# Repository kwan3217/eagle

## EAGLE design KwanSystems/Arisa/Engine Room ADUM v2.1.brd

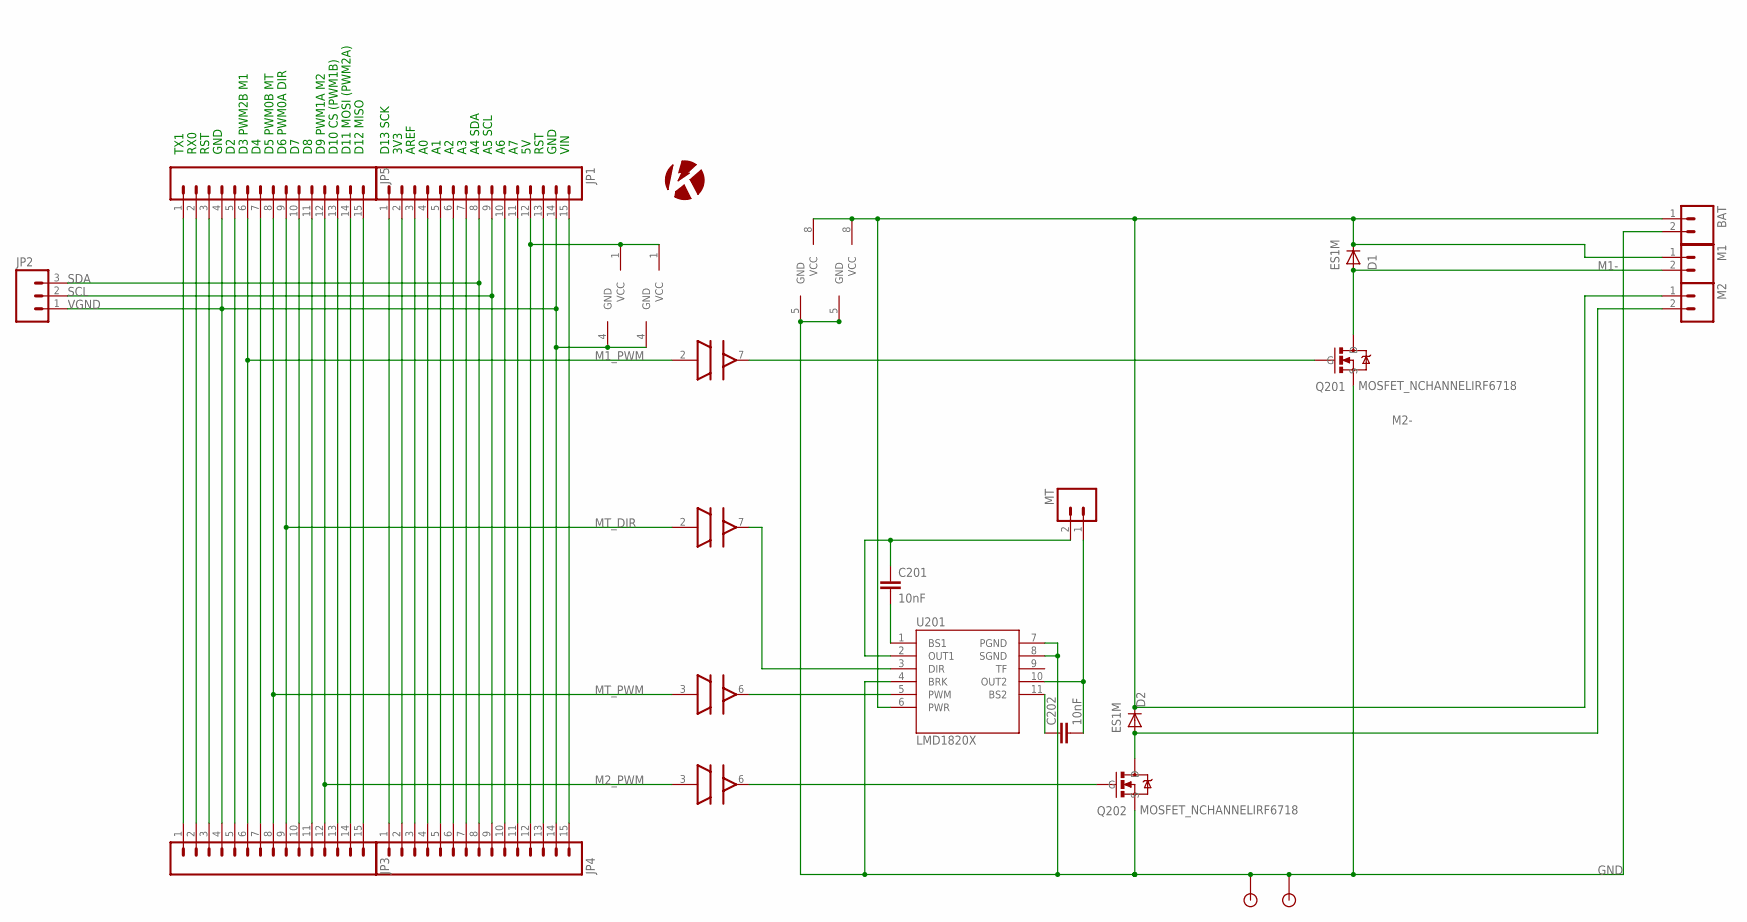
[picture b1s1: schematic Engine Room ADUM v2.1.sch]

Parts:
BAT: M02PTH4; 1X02_XTRA_BIG
C201, C202: 10nF; 0402-CAP
D1, D2: ES1M; DO-214AC
JP1, JP3, JP4, JP5: M15; 1X15
JP2: M03LOCK; 1X03_LOCK
M1, M2: M02PTH4; 1X02_XTRA_BIG
MT: M02PTH; 1X02
Q201, Q202: MOSFET_NCHANNELIRF6718; DIRECTFET_L6
U201: LMD1820X; TO-220-11LEAD
U$1: KWAN_CIRCLE
U$4, U$5: ADUM3221; SO8N
U$6, U$7: STANDOFF

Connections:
GND: BAT.2, Q201.S, Q202.S, U201.4 (BRK), U201.7 (PGND), U201.8 (SGND), U$4.5 (GND), U$5.5 (GND), U$6.P$1, U$7.P$1
M1-: D1.A, M1.2, Q201.D1 (D), Q201.D2 (D)
M1_PWM: JP3.6, JP5.6, U$4.2 (IN)
M2-: D2.A, M2.2, Q202.D1 (D), Q202.D2 (D)
M2_PWM: JP3.12, JP5.12, U$5.3 (IN)
MT_DIR: JP3.9, JP5.9, U$5.2 (IN)
MT_PWM: JP3.8, JP5.8, U$4.3 (IN)
unnamed: JP1.15, JP4.15
unnamed: Q201.G, U$4.7 (OUT)
unnamed: C202.1, U201.11 (BS2)
unnamed: Q202.G, U$5.6 (OUT)
unnamed: C201.2, U201.1 (BS1)
unnamed: U201.3 (DIR), U$5.7 (OUT)
unnamed: JP3.1, JP5.1
unnamed: JP3.2, JP5.2
unnamed: JP3.3, JP5.3
unnamed: U201.5 (PWM), U$4.6 (OUT)
unnamed: C201.1, MT.2, U201.2 (OUT1)
unnamed: C202.2, MT.1, U201.10 (OUT2)
unnamed: JP3.5, JP5.5
unnamed: JP3.15, JP5.15
unnamed: JP3.14, JP5.14
unnamed: JP3.13, JP5.13
unnamed: JP3.7, JP5.7
unnamed: JP3.10, JP5.10
unnamed: JP3.11, JP5.11
unnamed: JP1.13, JP4.13
unnamed: JP1.11, JP4.11
unnamed: JP1.10, JP4.10
unnamed: JP1.7, JP4.7
unnamed: JP1.6, JP4.6
unnamed: JP1.5, JP4.5
unnamed: JP1.4, JP4.4
unnamed: JP1.3, JP4.3
unnamed: JP1.2, JP4.2
unnamed: JP1.1, JP4.1
SCL: JP1.9, JP2.2, JP4.9
SDA: JP1.8, JP2.3, JP4.8
VCC: JP1.12, JP4.12, U$4.1 (VCC), U$5.1 (VCC)
VDD: BAT.1, D1.C, D2.C, M1.1, M2.1, U201.6 (PWR), U$4.8 (VCC), U$5.8 (VCC)
VGND: JP1.14, JP2.1, JP3.4, JP4.14, JP5.4, U$4.4 (GND), U$5.4 (GND)

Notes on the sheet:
VIN
GND
RST
A5 SCL
A4 SDA
AREF
3V3
D13 SCK
D12 MISO
D11 MOSI (PWM2A)
D10 CS (PWM1B)
D9 PWM1A M2
D6 PWM0A DIR
D5 PWM0B MT
D3 PWM2B M1
RX0
TX1

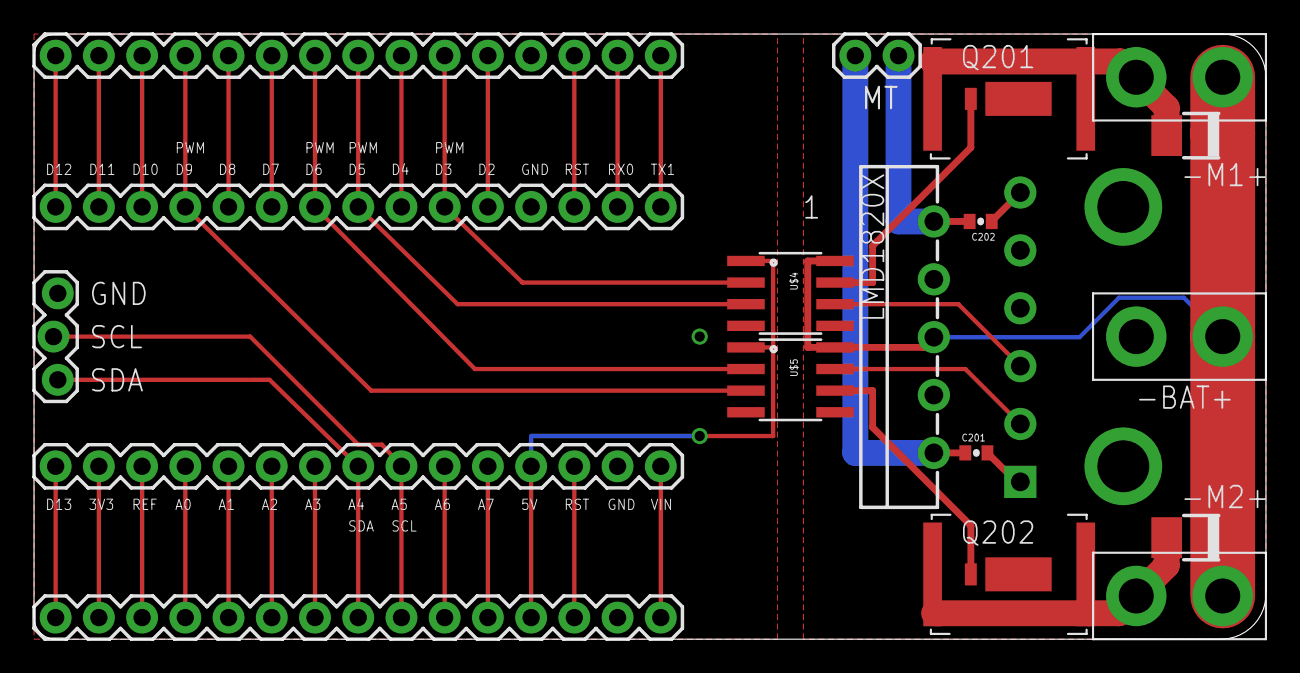
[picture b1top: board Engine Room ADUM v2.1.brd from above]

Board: 2 copper layers, 72.4 x 35.6 mm, 21 parts (1 on the bottom side), 41 nets.

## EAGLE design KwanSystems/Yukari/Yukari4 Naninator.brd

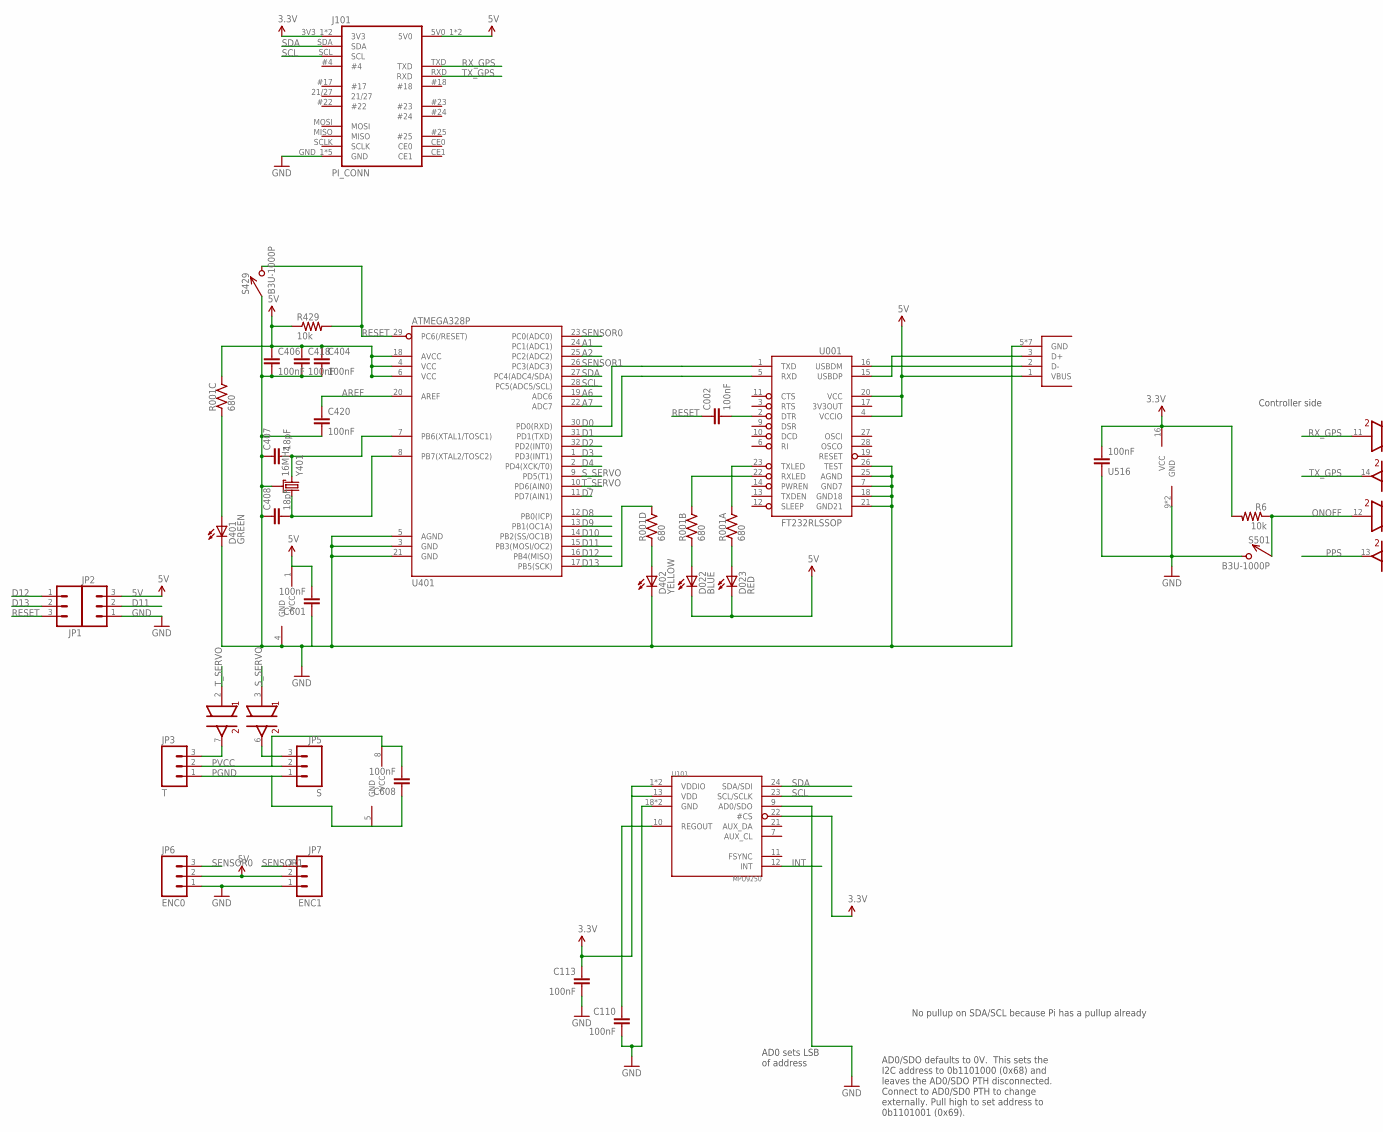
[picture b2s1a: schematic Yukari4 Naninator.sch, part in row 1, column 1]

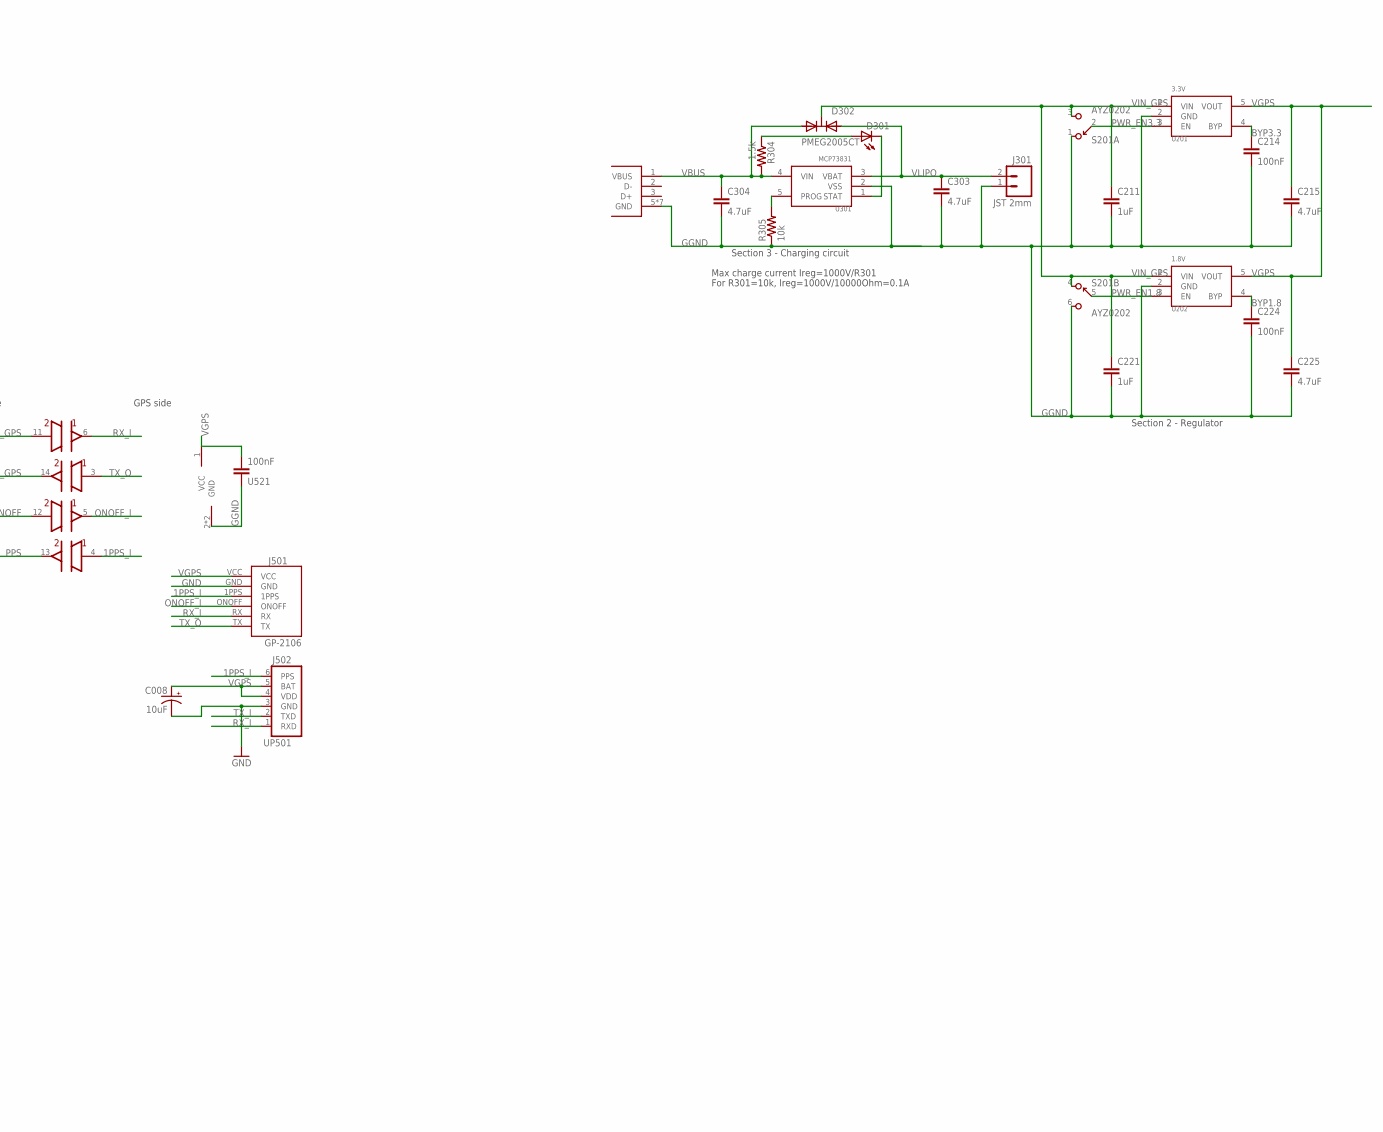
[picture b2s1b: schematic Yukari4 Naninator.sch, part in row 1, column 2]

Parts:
C002, C404, C406, C418, C420, C601, C608: 100nF; 0402-CAP; DIGIKEY 445-1268-1-ND
C008: 10uF; EIA3216
C110, C113: 100nF; 0402-CAP
C211, C221: 1uF; 0402-CAP; DIGIKEY 445-4114-1-ND
C214, C224: 100nF; 0402-CAP; DIGIKEY 445-1265-1-ND
C215, C225, C303, C304: 4.7uF; 0402-CAP; DIGIKEY 445-7395-1-ND
C407, C408: 18pF; 0402-CAP; DIGIKEY 445-1238-1-ND
D022: BLUE; LED-0603; DIGIKEY 350-2037-1-ND
D023: RED; LED-0603; DIGIKEY 754-1359-1-ND
D301: YELLOW; LED-0603; DIGIKEY 350-2032-1-ND
D302: PMEG2005CT; SOT-23-3
D401: GREEN; LED-0603; DIGIKEY 350-2036-1-ND
D402: YELLOW; LED-0603; DIGIKEY 754-1124-1-ND
J001, J302: USB_MICROB_JST; UB-MC5BR3-SD204-4S; DIGIKEY 455-2562-1-ND
J101: PI_CONN
J301: JST 2mm; JST-2-SMD; DIGIKEY 455-1749-1-ND
J501: GP-2106
J502: UP501
JP1, JP2: M03PTH; 1X03; DIGIKEY $NOPART
JP3: T; 1X03; DIGIKEY $NOPART
JP5: S; 1X03; DIGIKEY $NOPART
JP6: ENC0; 1X03; DIGIKEY $NOPART
JP7: ENC1; 1X03; DIGIKEY $NOPART
R001: 680; CRA04; DIGIKEY CRA4S8680CT-ND
R6: 10k; 0402-RES
R304: 1.5k; 0402-RES; DIGIKEY P1.50KLCT-ND
R305, R429: 10k; 0402-RES; DIGIKEY P10.0KLCT-ND
S201: AYZ0202
S429, S501: B3U-1000P
U001: FT232RLSSOP; SSOP28DB; DIGIKEY 768-1007-1-ND
U101: MPU9250; LQFN_3MM_3MM
U201: 3.3V; SOT-23-5; DIGIKEY 576-1910-1-ND
U202: 1.8V; SOT-23-5; DIGIKEY 576-1910-1-ND
U301: MCP73831; SOT-23-5; DIGIKEY 576-1910-1-ND
U401: ATMEGA328P; TQFP32-08; DIGIKEY ATMEGA328P-15AZCT-ND
U501: ADUM242E; 16-SOIC-W
U516, U521: 100nF; 0402-CAP; DIGIKEY 445-1268-1-ND
U601: ADUM3221; SO8N
Y401: 16MHz; CRYSTAL_SMD_2MM_2_5MM; DIGIKEY 478-6955-1-ND

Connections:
1PPS_I: J501.1PPS, J502.6 (PPS), U501.4 (IN)
3.3V: C113.1, J101.3V3_1 (3V3), J101.3V3_2 (3V3), R6.2, U101.1 (VDDIO), U101.8 (VDDIO), U101.13 (VDD), U101.22 (#CS), U501.16 (VCC), U516.2
5V: C404.1, C406.1, C418.1, C601.2, D022.C, D023.C, J001.1 (VBUS), J101.5V0_1 (5V0), J101.5V0_2 (5V0), JP2.3, JP6.2, JP7.2, R001.6 (2), R429.1, U001.4 (VCCIO), U001.20 (VCC), U401.4 (VCC), U401.6 (VCC), U401.18 (AVCC), U601.1 (VCC)
A1: U401.24 (PC1(ADC1))
A2: U401.25 (PC2(ADC2))
A6: U401.19 (ADC6)
A7: U401.22 (ADC7)
AREF: C420.1, U401.20 (AREF)
BYP1.8: C224.1, U202.4 (BYP)
BYP3.3: C214.1, U201.4 (BYP)
D0: U001.1 (TXD), U401.30 (PD0(RXD))
D1: U001.5 (RXD), U401.31 (PD1(TXD))
D2: U401.32 (PD2(INT0))
D3: U401.1 (PD3(INT1))
D4: U401.2 (PD4(XCK/T0))
D7: U401.11 (PD7(AIN1))
D8: U401.12 (PB0(ICP))
D9: U401.13 (PB1(OC1A))
D10: U401.14 (PB2(SS/OC1B))
D11: JP2.2, U401.15 (PB3(MOSI/OC2))
D12: JP1.1, U401.16 (PB4(MISO))
D13: JP1.2, R001.5 (2), U401.17 (PB5(SCK))
DTR#: C002.2, U001.2 (DTR)
GGND: C211.2, C214.2, C215.2, C221.2, C224.2, C225.2, C303.2, C304.2, J301.1, J302.5 (GND), J302.P$6 (GND), J302.P$7 (GND), J302.P$8 (GND), J302.P$9 (GND), J302.P$10 (GND), J302.P$11 (GND), R305.1, S201.1, S201.6, U201.2 (GND), U202.2 (GND), U301.2 (VSS), U501.2 (GND), U501.8 (GND), U521.1
GND: C008.C (-), C110.2, C113.2, C404.2, C406.2, C407.1, C408.1, C418.2, C420.2, C601.1, D401.C, D402.C, J001.5 (GND), J001.P$6 (GND), J001.P$7 (GND), J001.P$8 (GND), J001.P$9 (GND), J001.P$10 (GND), J001.P$11 (GND), J101.GND_1 (GND), J101.GND_2 (GND), J101.GND_3 (GND), J101.GND_4 (GND), J101.GND_5 (GND), J501.GND, J502.3 (GND), JP2.1, JP6.1, JP7.1, S429.P$1 (1), S501.P$2 (2), U001.7 (GND7), U001.18 (GND18), U001.21 (GND21), U001.25 (AGND), U001.26 (TEST), U101.9 (AD0/SDO), U101.18 (GND), U101.20 (GND), U401.3 (GND), U401.5 (AGND), U401.21 (GND), U501.9 (GND), U501.15 (GND), U516.1, U601.4 (GND), Y401.2 (GND), Y401.4 (GND)
INT: U101.12 (INT)
unnamed: C407.2, U401.7 (PB6(XTAL1/TOSC1)), Y401.3 (2)
unnamed: C408.2, U401.8 (PB7(XTAL2/TOSC2)), Y401.1
unnamed: J001.3 (D+), U001.15 (USBDP)
unnamed: J001.2 (D-), U001.16 (USBDM)
unnamed: D401.A, R001.3 (1)
unnamed: JP5.3, U601.6 (OUT)
unnamed: JP3.3, U601.7 (OUT)
unnamed: D402.A, R001.4 (1)
unnamed: D023.A, R001.1
unnamed: R305.2, U301.5 (PROG)
unnamed: D022.A, R001.2 (1)
unnamed: D301.C, U301.1 (STAT)
unnamed: D301.A, R304.1
ONOFF: R6.1, S501.P$1 (1), U501.12 (IN)
ONOFF_I: J501.ONOFF, U501.5 (OUT)
PGND: C608.1, JP3.1, JP5.1, U601.5 (GND)
PPS: U501.13 (OUT)
PVCC: C608.2, JP3.2, JP5.2, U601.8 (VCC)
PWR_EN1.8: S201.5, U202.3 (EN)
PWR_EN3.3: S201.2, U201.3 (EN)
REGOUT: C110.1, U101.10 (REGOUT)
RESET: C002.1, JP1.3, R429.2, S429.P$2 (2), U401.29 (PC6(/RESET))
RXLED1: R001.7 (2), U001.22 (RXLED)
RX_GPS: J101.TXD, U501.11 (IN)
RX_I: J501.RX, J502.1 (RXD), U501.6 (OUT)
SCL: J101.SCL, U101.23 (SCL/SCLK), U401.28 (PC5(ADC5/SCL))
SDA: J101.SDA, U101.24 (SDA/SDI), U401.27 (PC4(ADC4/SDA))
SENSOR0: JP6.3, U401.23 (PC0(ADC0))
SENSOR1: JP7.3, U401.26 (PC3(ADC3))
S_SERVO: U401.9 (PD5(T1)), U601.3 (IN)
TXLED1: R001.8 (2), U001.23 (TXLED)
TX_GPS: J101.RXD, U501.14 (OUT)
TX_I: J502.2 (TXD)
TX_O: J501.TX, U501.3 (IN)
T_SERVO: U401.10 (PD6(AIN0)), U601.2 (IN)
VBUS: C304.1, D302.1 (A1), J302.1 (VBUS), R304.2, U301.4 (VIN)
VGPS: C008.A (+), C215.1, C225.1, J501.VCC, J502.4 (VDD), J502.5 (BAT), U201.5 (VOUT), U202.5 (VOUT), U501.1 (VCC), U521.2
VIN_GPS: C211.1, C221.1, D302.3 (K), S201.3, S201.4, U201.1 (VIN), U202.1 (VIN)
VLIPO: C303.1, D302.2 (A2), J301.2, U301.3 (VBAT)

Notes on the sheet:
AD0/SDO defaults to 0V. This sets the I2C address to 0b1101000 (0x68) and leaves the AD0/SDO PTH disconnected. Connect to AD0/SD0 PTH to change externally. Pull high to set address to 0b1101001 (0x69).
AD0 sets LSB of address
No pullup on SDA/SCL because Pi has a pullup already
GPS side
Controller side
Section 3 - Charging circuit
Max charge current Ireg=1000V/R301
For R301=10k, Ireg=1000V/10000Ohm=0.1A
Section 2 - Regulator

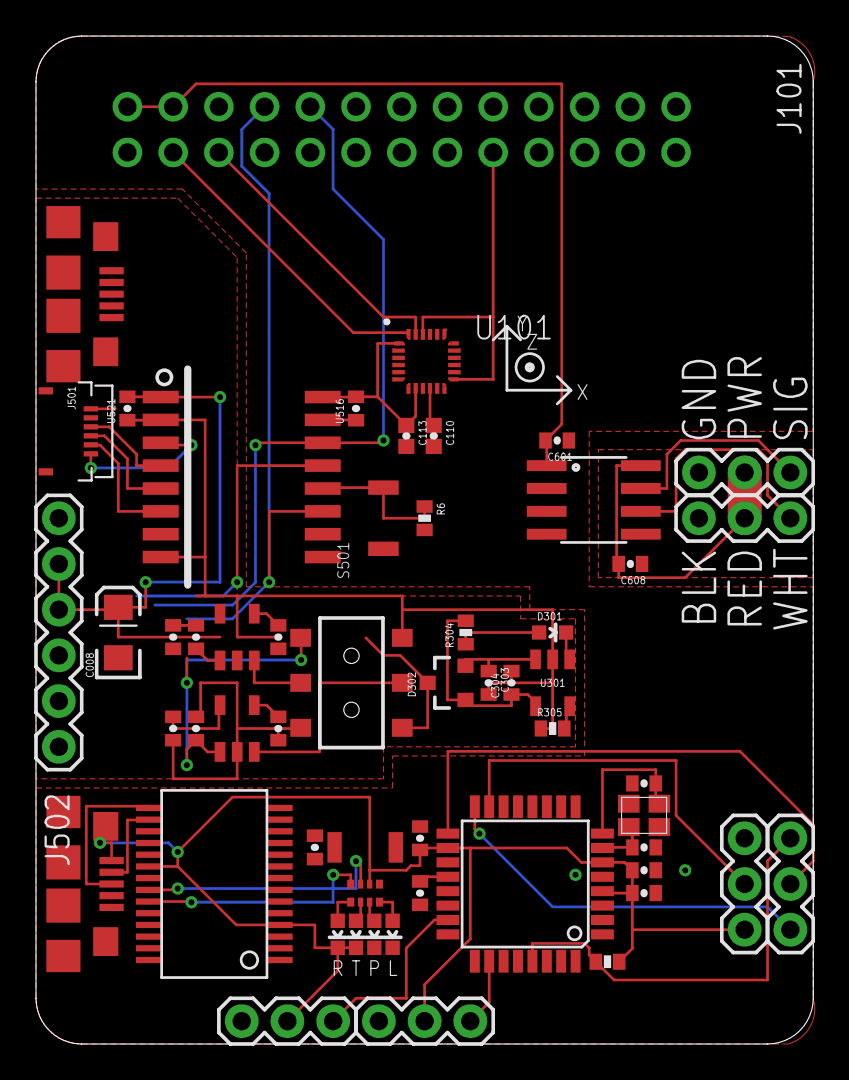
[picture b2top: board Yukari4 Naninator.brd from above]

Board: 2 copper layers, 43.2 x 56.0 mm, 58 parts (1 on the bottom side), 51 nets.

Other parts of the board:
U$2: AXES

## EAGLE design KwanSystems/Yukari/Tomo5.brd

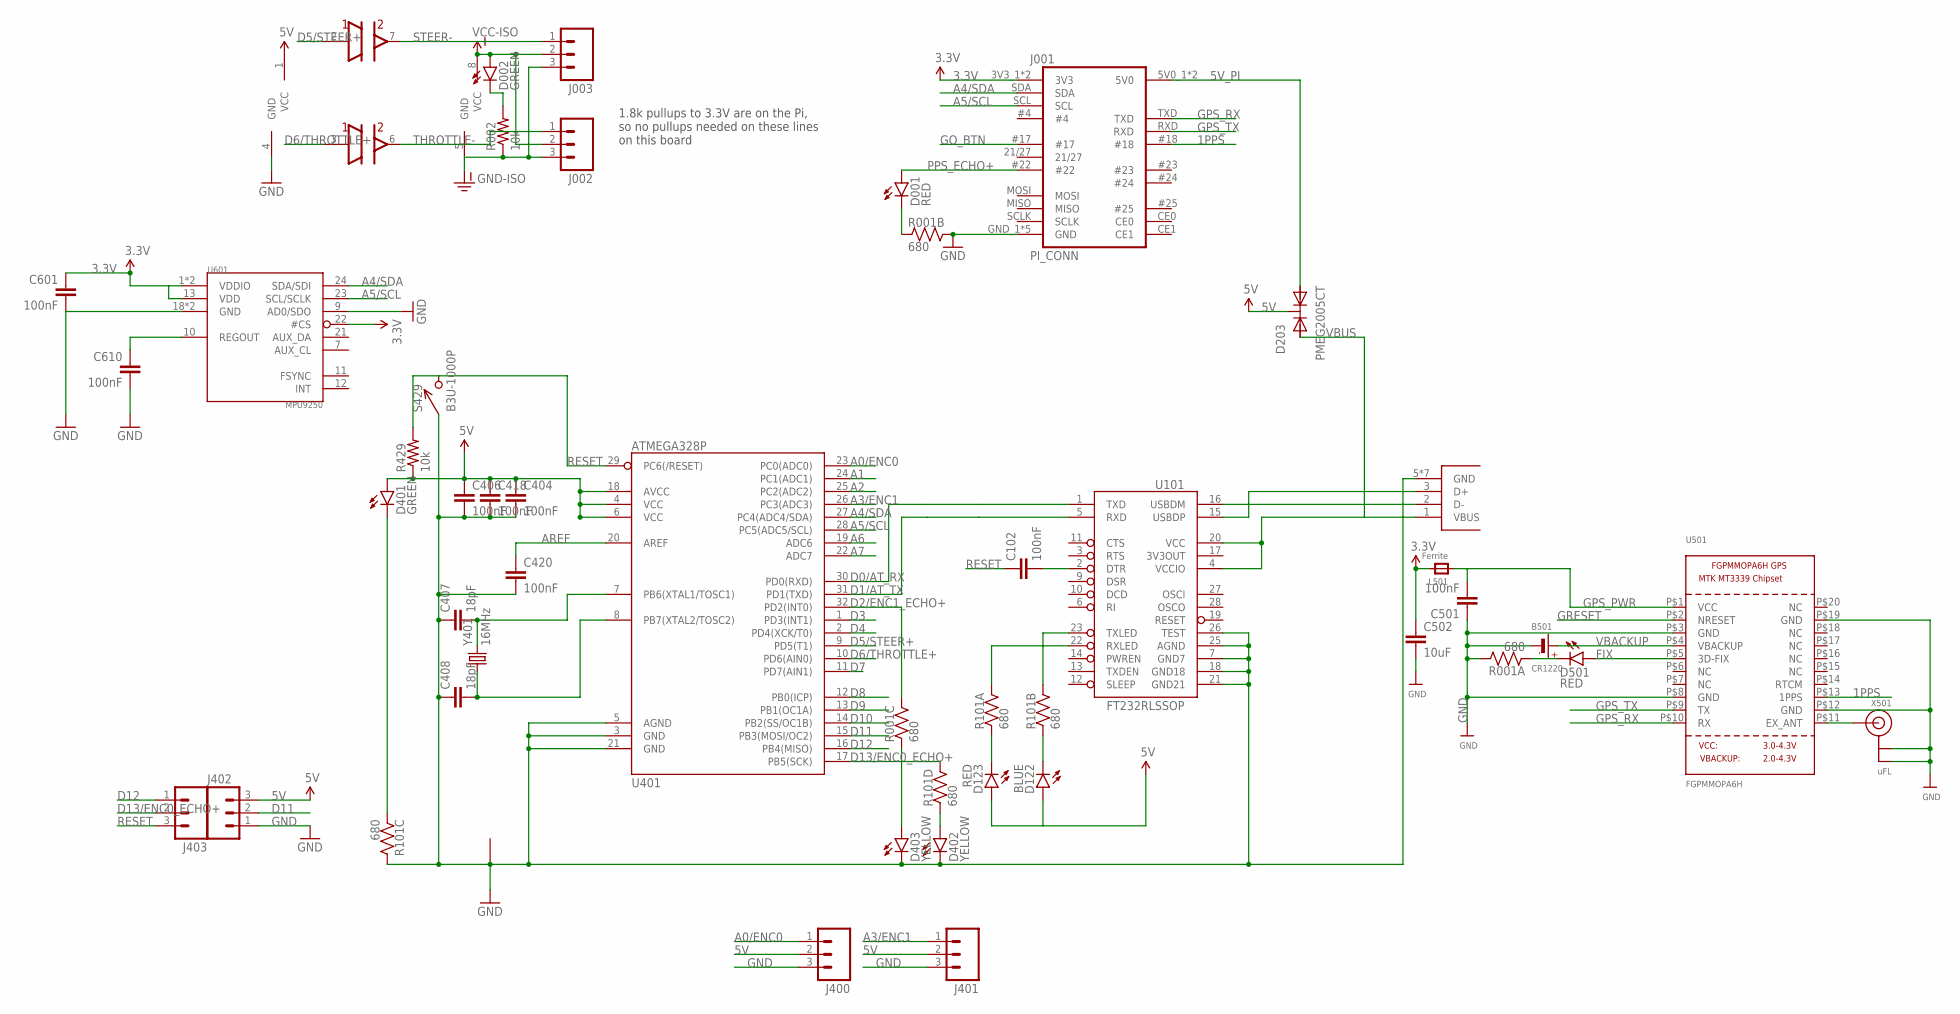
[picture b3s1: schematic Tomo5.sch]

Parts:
B501: CR1220; CR1220-2
C102, C404, C406, C418, C420, C501: 100nF; 0402-CAP; DIGIKEY 445-1268-1-ND
C407, C408: 18pF; 0402-CAP; DIGIKEY 445-1238-1-ND
C502: 10uF; 1206
C601: 100nF; 0603-CAP
C610: 100nF; 0402-CAP
D001, D501: RED; LED-0603
D002, D401: GREEN; LED-0603; DIGIKEY 350-2036-1-ND
D122: BLUE; LED-0603; DIGIKEY 350-2037-1-ND
D123: RED; LED-0603; DIGIKEY 754-1359-1-ND
D203: PMEG2005CT; SOT-23-3
D402, D403: YELLOW; LED-0603; DIGIKEY 754-1124-1-ND
J001: PI_CONN
J002, J003, J400, J401, J402, J403: M03PTH; 1X03; DIGIKEY $NOPART
J101: USB_MICROB_JST; UB-MC5BR3-SD204-4S; DIGIKEY 455-2562-1-ND
L501: Ferrite; 0805-NO
R001, R101: 680; CRA04; DIGIKEY CRA4S8680CT-ND
R002, R429: 10k; 0402-RES; DIGIKEY P10.0KLCT-ND
S429: B3U-1000P
U101: FT232RLSSOP; SSOP28DB; DIGIKEY 768-1007-1-ND
U401: ATMEGA328P; TQFP32-08; DIGIKEY ATMEGA328P-15AZCT-ND
U501: FGPMMOPA6H
U601: MPU9250; LQFN_3MM_3MM
U$7: ADUM3221; SO8N
X501: uFL; U.FL
Y401: 16MHz; CRYSTAL_SMD_2MM_2_5MM; DIGIKEY 478-6955-1-ND

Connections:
1PPS: J001.#18, U501.P$13 (1PPS)
3.3V: C502.1, C601.1, J001.3V3_1 (3V3), J001.3V3_2 (3V3), L501.2, U601.1 (VDDIO), U601.8 (VDDIO), U601.13 (VDD), U601.22 (#CS)
5V: C404.1, C406.1, C418.1, D122.A, D123.A, D203.3 (K), D401.A, J400.2, J401.2, J402.3, R429.1, U401.4 (VCC), U401.6 (VCC), U401.18 (AVCC), U$7.1 (VCC)
5V_PI: D203.1 (A1), J001.5V0_1 (5V0), J001.5V0_2 (5V0)
A0/ENC0: J400.1, U401.23 (PC0(ADC0))
A1: U401.24 (PC1(ADC1))
A2: U401.25 (PC2(ADC2))
A3/ENC1: J401.1, U401.26 (PC3(ADC3))
A4/SDA: J001.SDA, U401.27 (PC4(ADC4/SDA)), U601.24 (SDA/SDI)
A5/SCL: J001.SCL, U401.28 (PC5(ADC5/SCL)), U601.23 (SCL/SCLK)
A6: U401.19 (ADC6)
A7: U401.22 (ADC7)
AREF: C420.1, U401.20 (AREF)
D0/AT_RX: U101.1 (TXD), U401.30 (PD0(RXD))
D1/AT_TX: U101.5 (RXD), U401.31 (PD1(TXD))
D2/ENC1_ECHO+: R001.6 (2), U401.32 (PD2(INT0))
D3: U401.1 (PD3(INT1))
D4: U401.2 (PD4(XCK/T0))
D5/STEER+: U401.9 (PD5(T1)), U$7.2 (IN)
D6/THROTTLE+: U401.10 (PD6(AIN0)), U$7.3 (IN)
D7: U401.11 (PD7(AIN1))
D8: U401.12 (PB0(ICP))
D9: U401.13 (PB1(OC1A))
D10: U401.14 (PB2(SS/OC1B))
D11: J402.2, U401.15 (PB3(MOSI/OC2))
D12: J403.1, U401.16 (PB4(MISO))
D13/ENC0_ECHO+: J403.2, R101.5 (2), U401.17 (PB5(SCK))
DTR#: C102.2, U101.2 (DTR)
ENC0_ECHO-: D402.A, R101.4 (1)
FIX: D501.A, U501.P$5 (3D-FIX)
GND: B501.-, C404.2, C406.2, C407.1, C408.1, C418.2, C420.2, C501.1, C502.2, C601.2, C610.2, D402.C, D403.C, J001.GND_1 (GND), J001.GND_2 (GND), J001.GND_3 (GND), J001.GND_4 (GND), J001.GND_5 (GND), J101.5 (GND), J101.P$6 (GND), J101.P$7 (GND), J101.P$8 (GND), J101.P$9 (GND), J101.P$10 (GND), J101.P$11 (GND), J400.3, J401.3, J402.1, R001.7 (2), R001.8 (2), R101.6 (2), S429.P$1 (1), U101.7 (GND7), U101.18 (GND18), U101.21 (GND21), U101.25 (AGND), U101.26 (TEST), U401.3 (GND), U401.5 (AGND), U401.21 (GND), U501.P$3 (GND), U501.P$8 (GND), U501.P$12 (GND), U501.P$19 (GND), U601.9 (AD0/SDO), U601.18 (GND), U601.20 (GND), U$7.4 (GND), X501.1 (GND), X501.2 (GND), Y401.2 (1), Y401.4 (1)
GND-ISO: J002.3, J003.3, R002.1, U$7.5 (GND)
GO_BTN: J001.#17
GPS_PWR: C501.2, L501.1, U501.P$1 (VCC)
GPS_RX: J001.TXD, U501.P$10 (RX)
GPS_TX: J001.RXD, U501.P$9 (TX)
GRESET: U501.P$2 (NRESET)
IPWR-: D002.C, R002.2
unnamed: C407.2, U401.7 (PB6(XTAL1/TOSC1)), Y401.3 (2)
unnamed: C408.2, U401.8 (PB7(XTAL2/TOSC2)), Y401.1
unnamed: J101.3 (D+), U101.15 (USBDP)
unnamed: J101.2 (D-), U101.16 (USBDM)
unnamed: D401.C, R101.3 (1)
unnamed: D501.C, R001.1
unnamed: U501.P$11 (EX_ANT), X501.3 (SIGNAL)
unnamed: D403.A, R001.3 (1)
PPS_ECHO+: D001.A, J001.#22
PPS_ECHO-: D001.C, R001.2 (1)
REGOUT: C610.1, U601.10 (REGOUT)
RESET: C102.1, J403.3, R429.2, S429.P$2 (2), U401.29 (PC6(/RESET))
RXLED+: D123.C, R101.1
RXLED-: R101.8 (2), U101.22 (RXLED)
STEER-: J003.1, U$7.7 (OUT)
THROTTLE-: J002.1, U$7.6 (OUT)
TXLED+: D122.C, R101.2 (1)
TXLED-: R101.7 (2), U101.23 (TXLED)
VBACKUP: B501.+, U501.P$4 (VBACKUP)
VBUS: D203.2 (A2), J101.1 (VBUS), U101.4 (VCCIO), U101.20 (VCC)
VCC-ISO: D002.A, J002.2, J003.2, U$7.8 (VCC)

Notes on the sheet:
1.8k pullups to 3.3V are on the Pi, so no pullups needed on these lines on this board

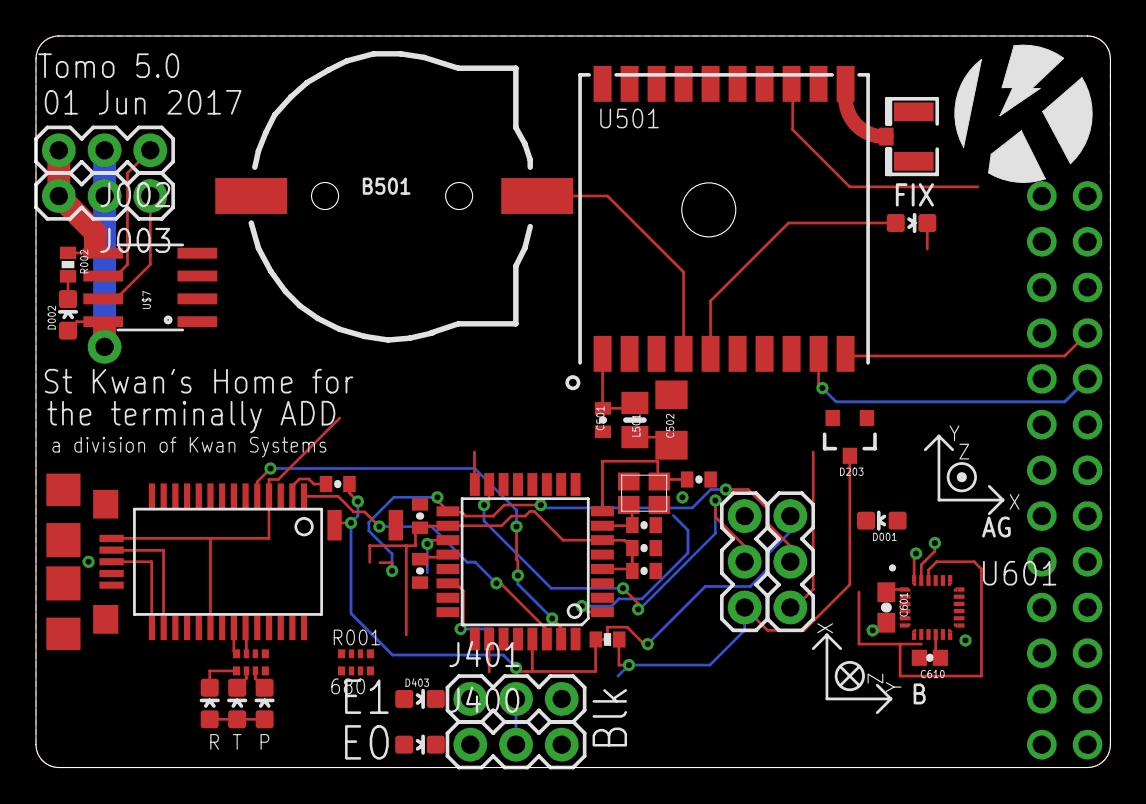
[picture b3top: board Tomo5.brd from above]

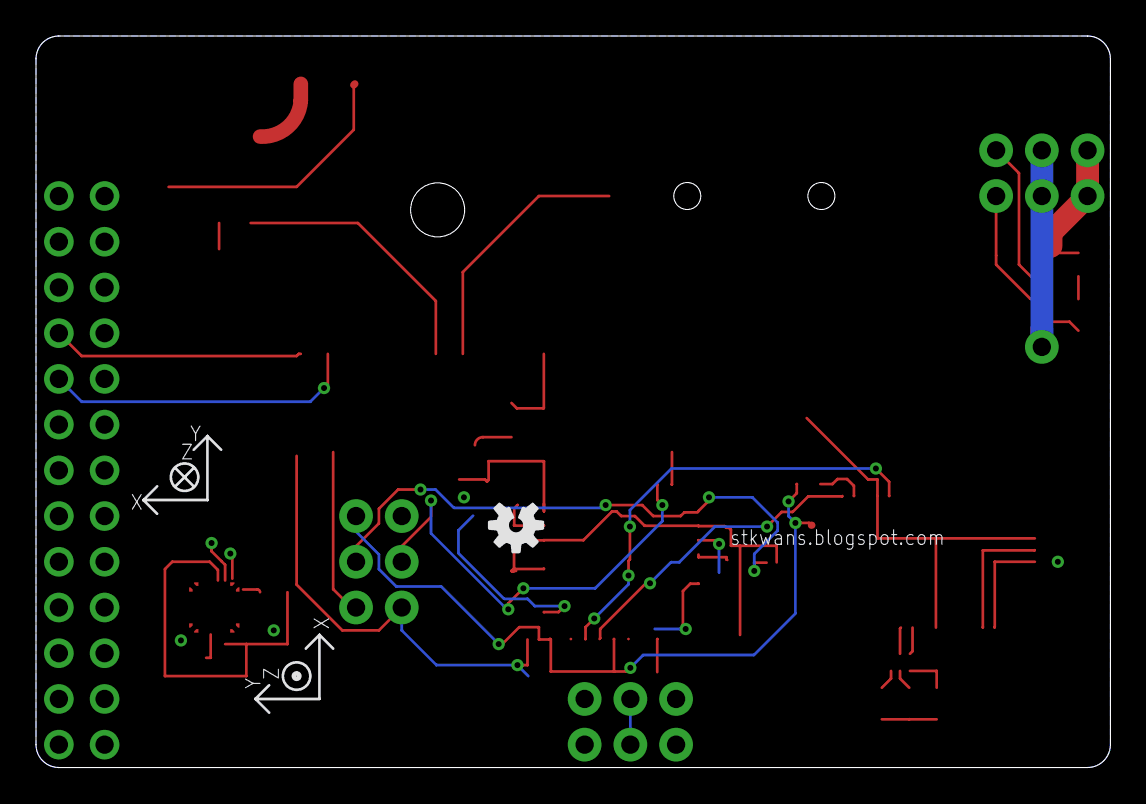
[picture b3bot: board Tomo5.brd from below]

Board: 2 copper layers, 59.7 x 40.6 mm, 46 parts (2 on the bottom side), 47 nets.

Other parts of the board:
U$1: KWAN_CIRCLE
U$2: OSHW-LOGO-S
U$3, U$4: AXES

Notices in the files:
parts and their libraries:
SparkFun-Connectors: Licensing: Creative Commons ShareAlike 4.0 International - https://creativecommons.org/licenses/by-sa/4.0
SparkFun-Connectors: Licensing: CC v3.0 Share-Alike You are welcome to use this library for commercial purposes.
